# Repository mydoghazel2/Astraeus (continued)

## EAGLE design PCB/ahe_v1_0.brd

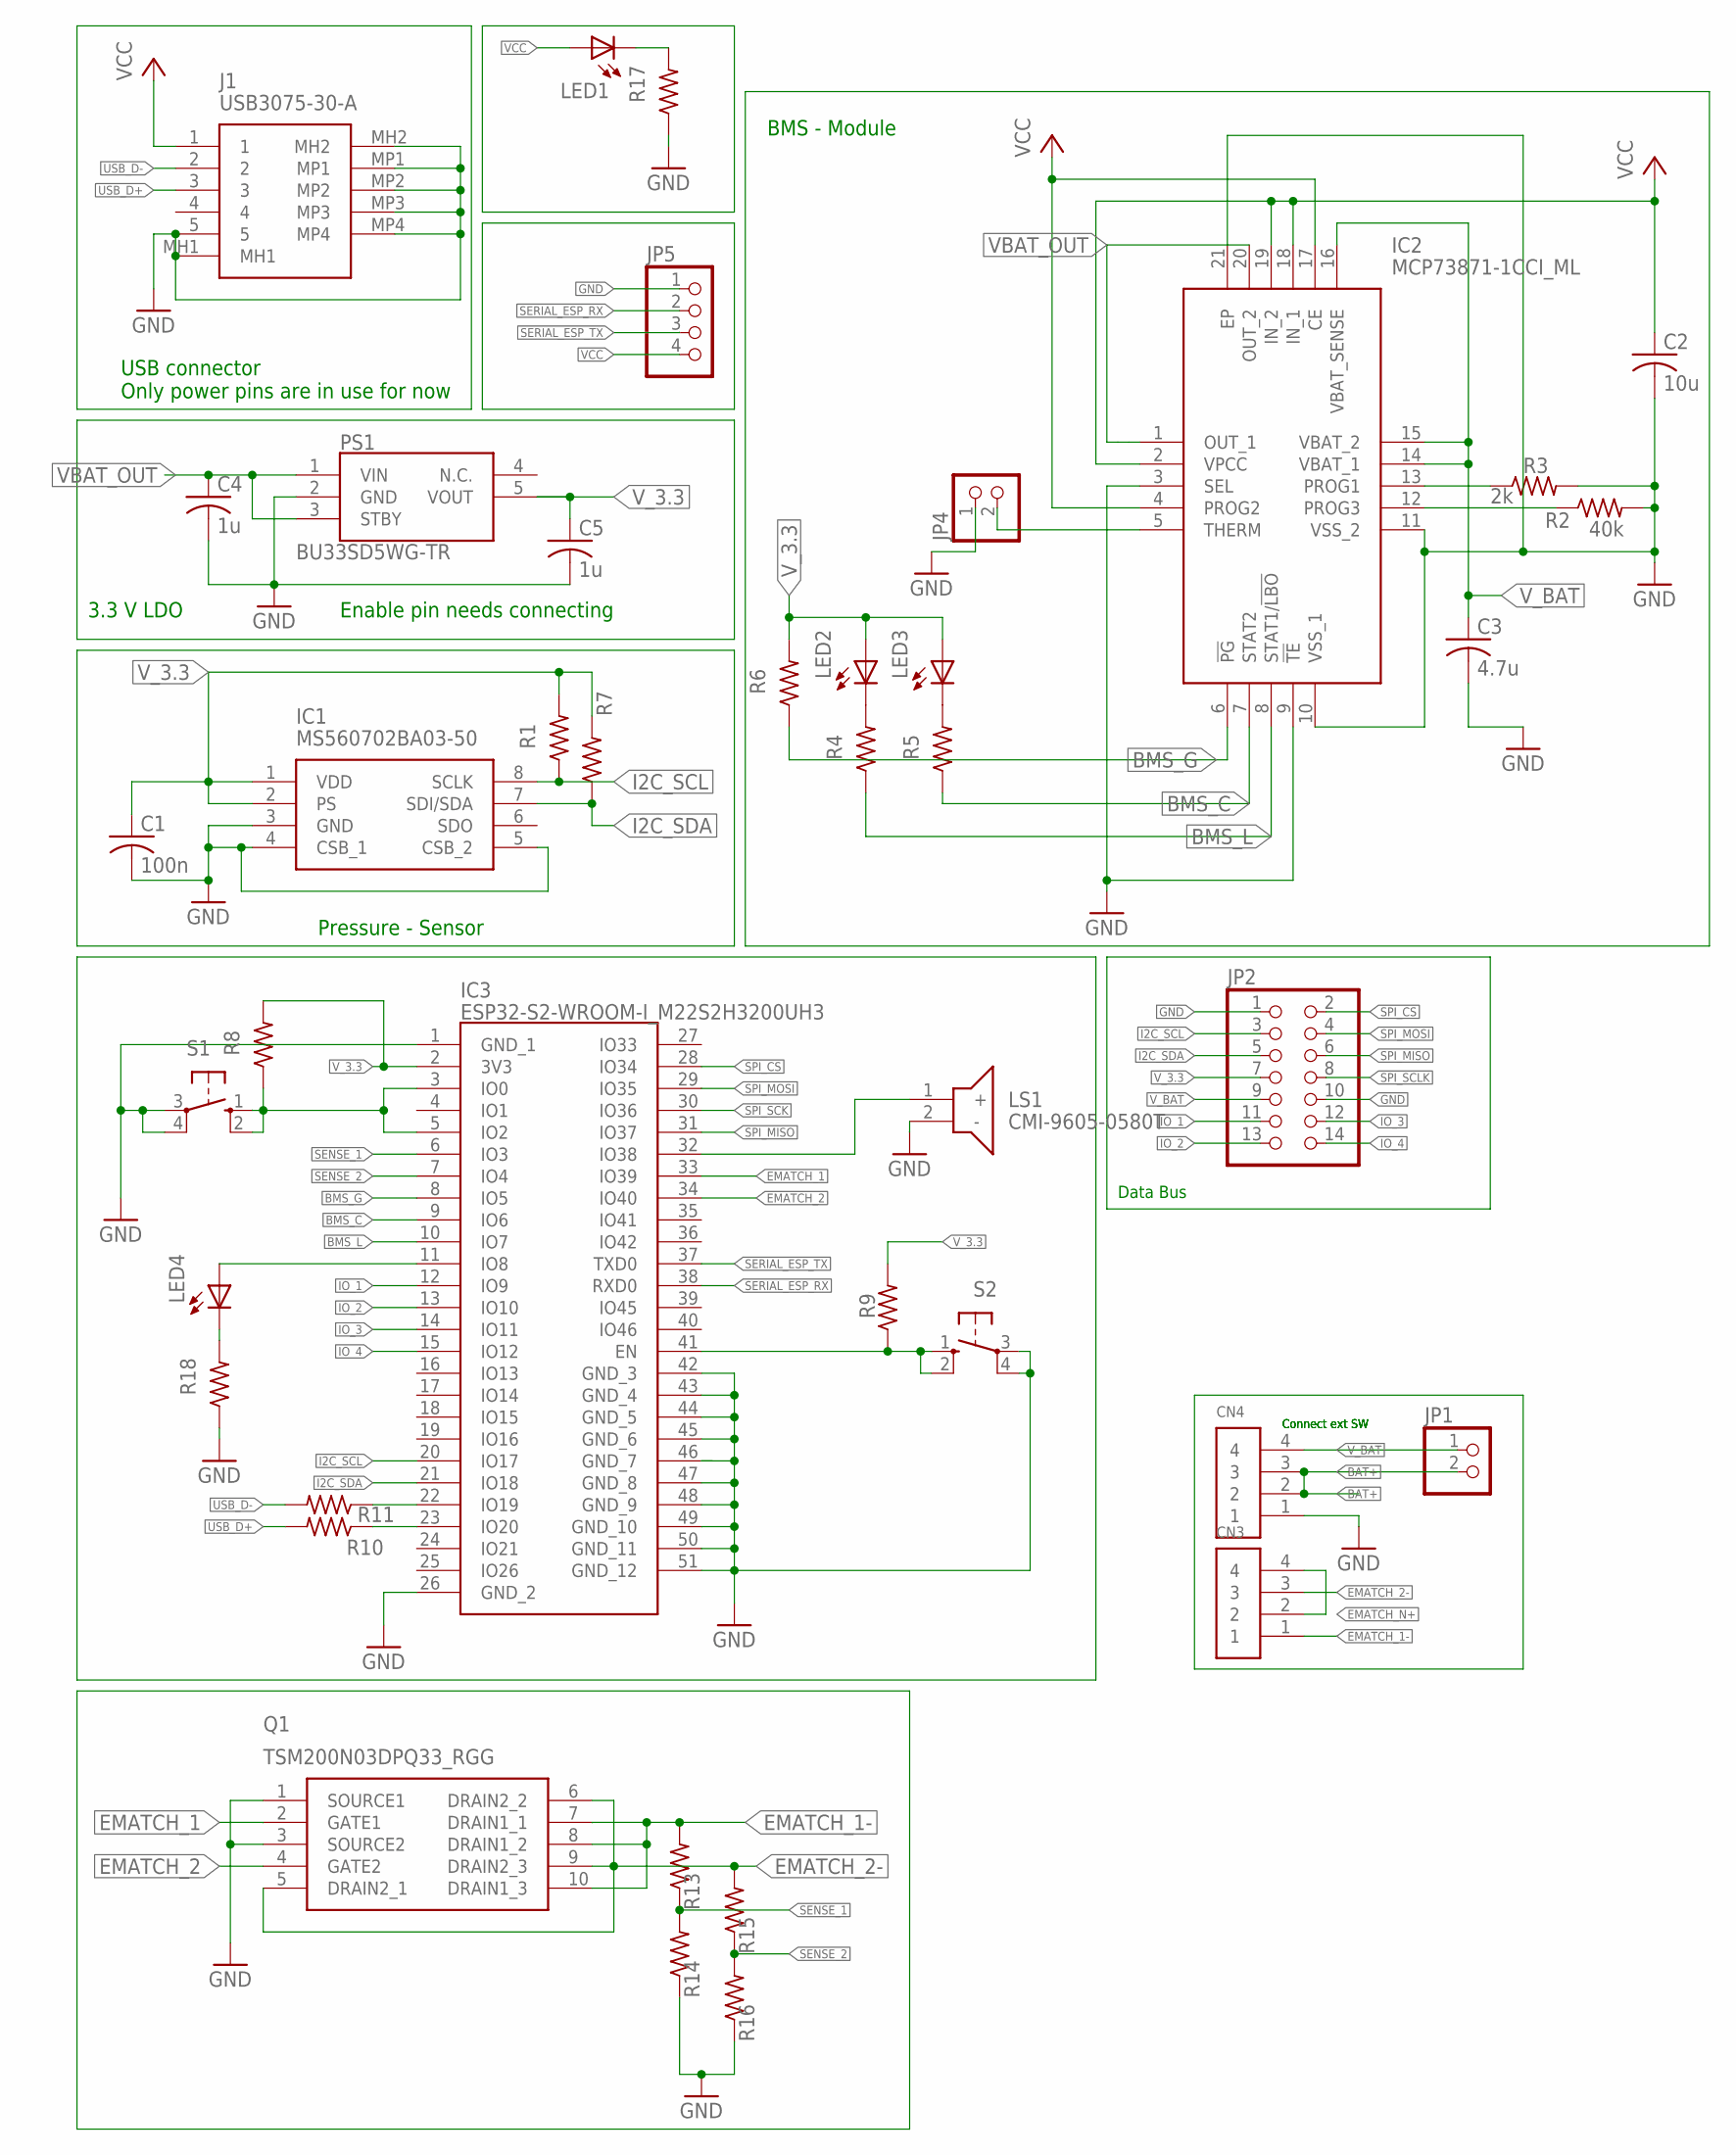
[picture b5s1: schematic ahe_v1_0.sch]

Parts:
C1: 100n; C0805
C2: 10u; C0805
C3: 4.7u; C0805
C4, C5: 1u; C0805
CN3, CN4: 1X4-3.5MM; 1X04-3.5MM
IC1: MS560702BA03-50; MS5607-02BA03
IC2: MCP73871-1CCI_ML; QFN50P400X400X100-21N
IC3: ESP32-S2-WROOM-I_M22S2H3200UH3; ESP32S2WROOMIM22S2H3200UH3Q0
J1: USB3075-30-A; USB307530A
JP1, JP4: PINHD-1X2; 1X02
JP2: PINHD-2X7; 2X07
JP5: PINHD-1X4; 1X04
LED1, LED2, LED3, LED4: LEDCHIPLED_0805; CHIPLED_0805
LS1: CMI-9605-0580T; CMI96050580T
PS1: BU33SD5WG-TR; SOT95P280X125-5N
Q1: TSM200N03DPQ33_RGG; TSM200N03DPQ33RGG
R1, R6, R7, R8, R9: 10k; R0805
R2: 40k; R0805
R3: 2k; R0805
R4, R5, R17, R18: 330; R0805
R10, R11: 33; R0805
R13, R15: 100k; R0805
R14, R16: 27k; R0805
S1, S2: 10-XX; B3F-10XX

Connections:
BAT+: CN4.2, CN4.3, JP1.2
BMS_C: IC2.7 (STAT2), IC3.9 (IO6), R5.1
BMS_G: IC2.6 (!PG), IC3.8 (IO5), R6.1
BMS_L: IC2.8 (STAT1/!LBO), IC3.10 (IO7), R4.1
EMATCH_1: IC3.33 (IO39), Q1.2 (GATE1)
EMATCH_1-: CN3.1, Q1.7 (DRAIN1_1), Q1.8 (DRAIN1_2), Q1.10 (DRAIN1_3), R13.2
EMATCH_2: IC3.34 (IO40), Q1.4 (GATE2)
EMATCH_2-: CN3.3, Q1.5 (DRAIN2_1), Q1.6 (DRAIN2_2), Q1.9 (DRAIN2_3), R15.2
EMATCH_N+: CN3.2, CN3.4
GND: C1.2, C2.2, C3.2, C4.2, C5.2, CN4.1, IC1.3 (GND), IC1.4 (CSB_1), IC1.5 (CSB_2), IC2.3 (SEL), IC2.9 (!TE), IC2.10 (VSS_1), IC2.11 (VSS_2), IC2.21 (EP), IC3.1 (GND_1), IC3.26 (GND_2), IC3.42 (GND_3), IC3.43 (GND_4), IC3.44 (GND_5), IC3.45 (GND_6), IC3.46 (GND_7), IC3.47 (GND_8), IC3.48 (GND_9), IC3.49 (GND_10), IC3.50 (GND_11), IC3.51 (GND_12), J1.5, J1.MH1, J1.MH2, J1.MP1, J1.MP2, J1.MP3, J1.MP4, JP2.1, JP2.10, JP4.1, JP5.1, LS1.2 (-), PS1.2 (GND), Q1.1 (SOURCE1), Q1.3 (SOURCE2), R2.2, R3.2, R14.1, R16.1, R17.1, R18.1, S1.3, S1.4 (P1), S2.3, S2.4 (P1)
I2C_SCL: IC1.8 (SCLK), IC3.20 (IO17), JP2.3, R1.1
I2C_SDA: IC1.7 (SDI/SDA), IC3.21 (IO18), JP2.5, R7.1
IO_1: IC3.12 (IO9), JP2.11
IO_2: IC3.13 (IO10), JP2.13
IO_3: IC3.14 (IO11), JP2.12
IO_4: IC3.15 (IO12), JP2.14
unnamed: IC2.13 (PROG1), R3.1
unnamed: IC2.12 (PROG3), R2.1
unnamed: IC2.5 (THERM), JP4.2
unnamed: IC3.3 (IO0), IC3.5 (IO2), R8.1, S1.1 (S), S1.2 (S1)
unnamed: IC3.22 (IO19), R11.1
unnamed: IC3.23 (IO20), R10.1
unnamed: LED1.C, R17.2
unnamed: LED2.C, R4.2
unnamed: LED3.C, R5.2
unnamed: LED4.C, R18.2
unnamed: IC3.11 (IO8), LED4.A
unnamed: IC3.41 (EN), R9.1, S2.1 (S), S2.2 (S1)
SENSE_1: IC3.6 (IO3), R13.1, R14.2
SENSE_2: IC3.7 (IO4), R15.1, R16.2
SERIAL_ESP_RX: IC3.38 (RXD0), JP5.2
SERIAL_ESP_TX: IC3.37 (TXD0), JP5.3
SOUND: IC3.32 (IO38), LS1.1 (+)
SPI_CS: IC3.28 (IO34), JP2.2
SPI_MISO: IC3.31 (IO37), JP2.6
SPI_MOSI: IC3.29 (IO35), JP2.4
SPI_SCK: IC3.30 (IO36)
SPI_SCLK: JP2.8
USB_D+: J1.3, R10.2
USB_D-: J1.2, R11.2
VBAT_OUT: C4.1, IC2.1 (OUT_1), IC2.20 (OUT_2), PS1.1 (VIN), PS1.3 (STBY)
VCC: C2.1, IC2.2 (VPCC), IC2.4 (PROG2), IC2.17 (CE), IC2.18 (IN_1), IC2.19 (IN_2), J1.1, JP5.4, LED1.A
V_3.3: C1.1, C5.1, IC1.1 (VDD), IC1.2 (PS), IC3.2 (3V3), JP2.7, LED2.A, LED3.A, PS1.5 (VOUT), R1.2, R6.2, R7.2, R8.2, R9.2
V_BAT: C3.1, CN4.4, IC2.14 (VBAT_1), IC2.15 (VBAT_2), IC2.16 (VBAT_SENSE), JP1.1, JP2.9

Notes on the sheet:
Pressure - Sensor
Enable pin needs connecting
USB connector Only power pins are in use for now
3.3 V LDO
BMS - Module
Data Bus
Connect ext SW

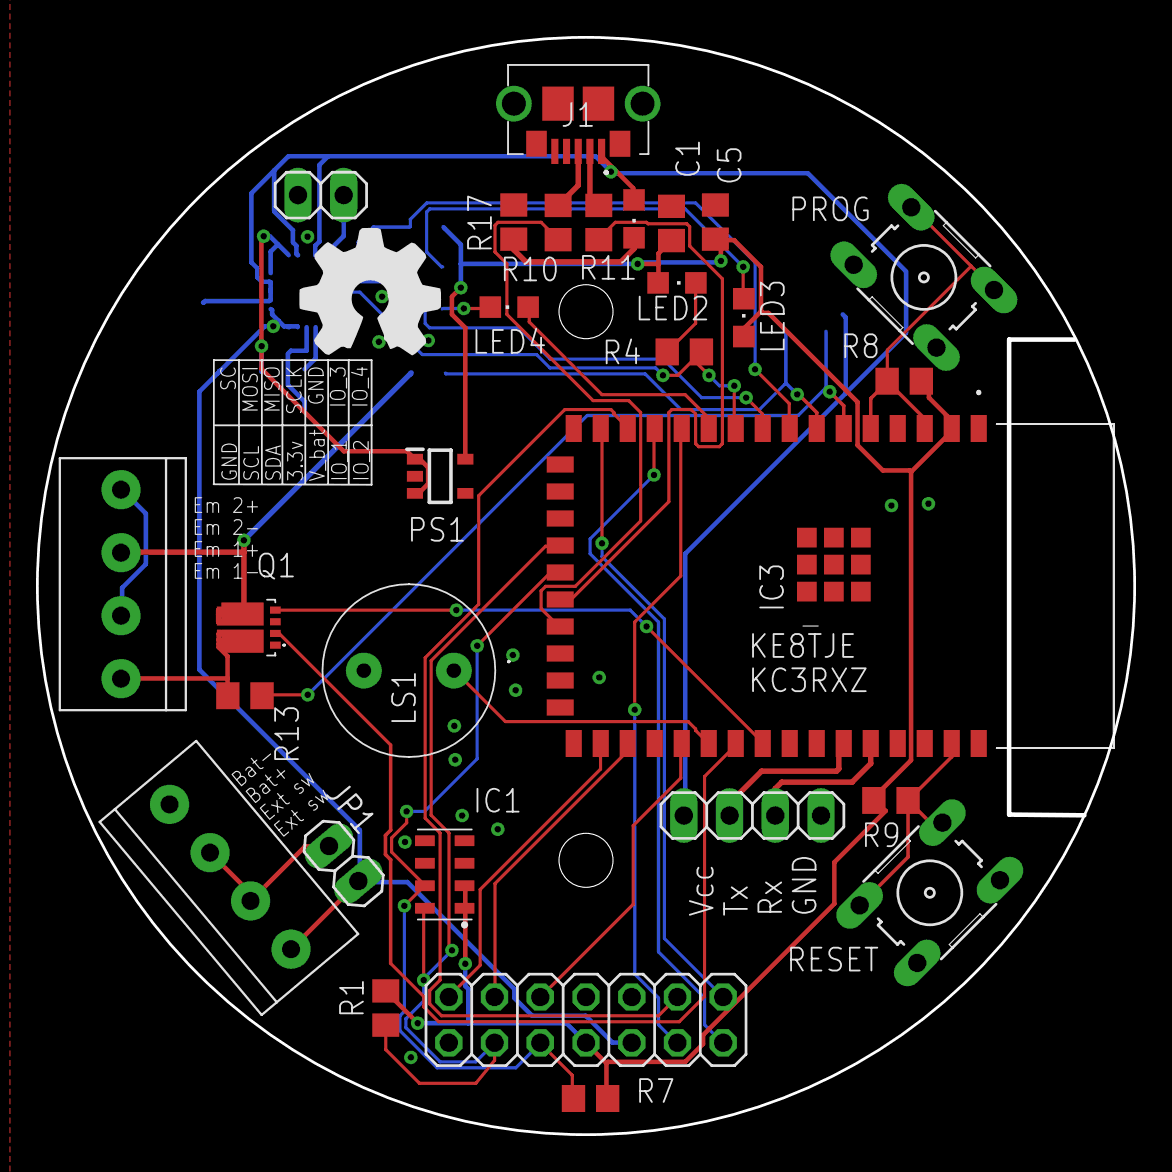
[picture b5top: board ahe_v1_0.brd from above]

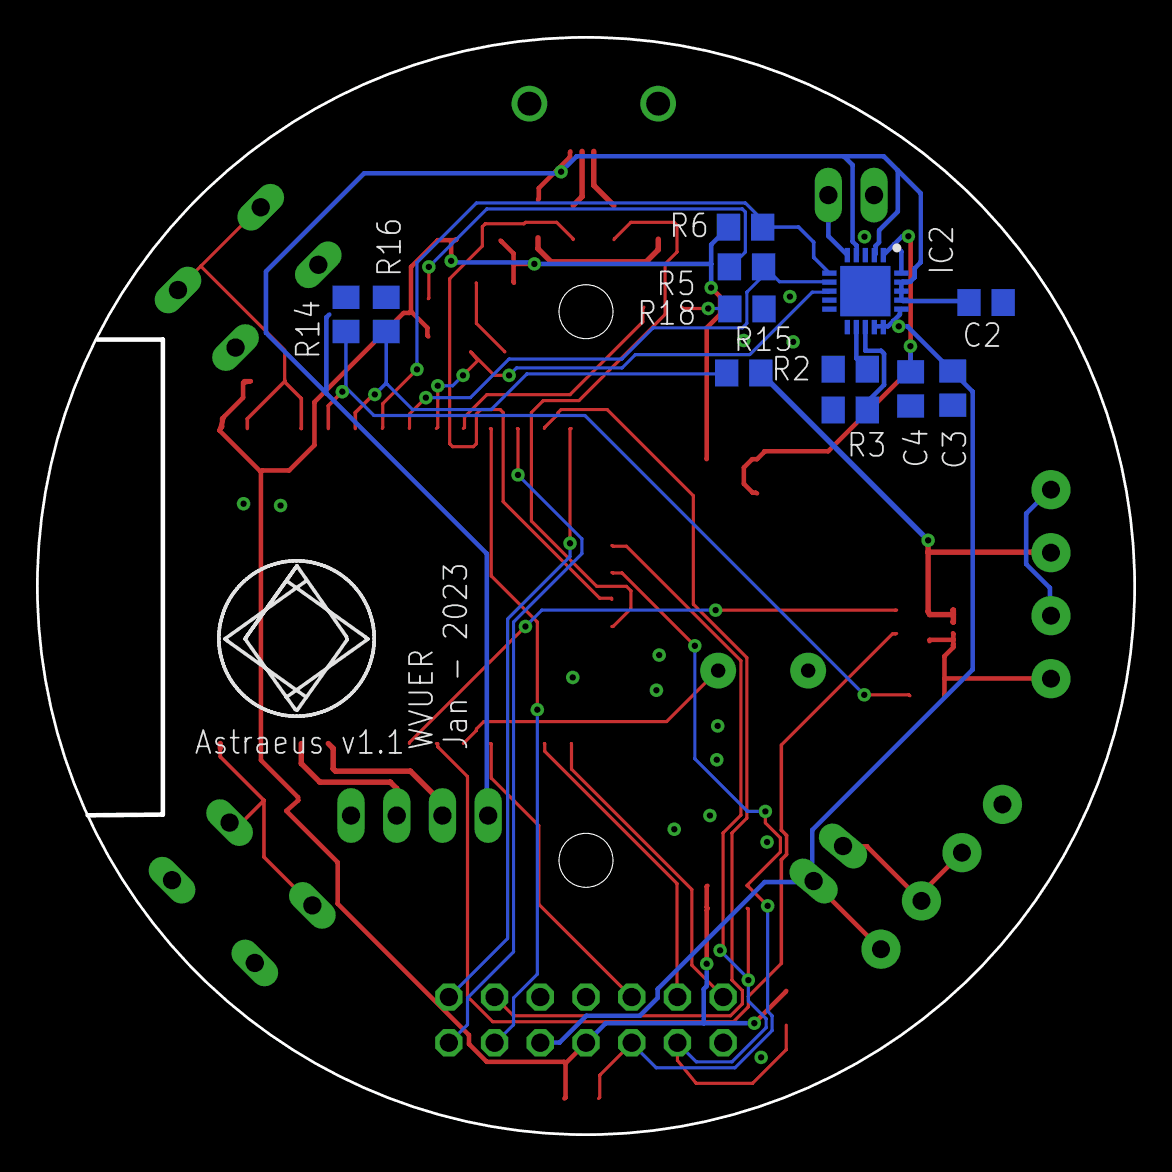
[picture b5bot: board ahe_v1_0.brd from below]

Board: 2 copper layers, 60.9 x 60.9 mm, 41 parts (12 on the bottom side), 42 nets.

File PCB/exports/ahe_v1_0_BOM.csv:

Qty,Value,Device,Package,Parts,Unit Price ,,MOUSER_PRICE-STOCK,Description,ARROW_PART_NUMBER,ARROW_PRICE-STOCK,DESCRIPTION,HEIGHT,MANUFACTURER_NAME,MANUFACTURER_PART_NUMBER,MF,MOUSER_PART_NUMBER,,MOUSER_TESTING_PART_NUMBER,MOUSER_TESTING_PRICE-STOCK,MPN,OC_FARNELL,OC_NEWARK,POPULARITY,SPICEPREFIX
2,,10-XX,B3F-10XX,"S1, S2",,0,,OMRON SWITCH,,,,,,,,,,,,B3F-1000,176432,36M3542,72,
1,,PINHD-1X4/90,1X04/90,JP3,,0,,PIN HEADER,,,,,,,,,,,,,,,9,
1,,PINHD-2X7,2X07,JP2,,0,,PIN HEADER,,,,,,,,,,,,,,,8,
1,0,R-US_R0805,R0805,R12,0,0,,"RESISTOR, American symbol",,,,,,,,,,,,,,,85,R
2,100k,R-US_R0805,R0805,"R13, R15",0.15,0.3,https://www.mouser.com/ProductDetail/Vishay-Draloric/RCG0805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,"RESISTOR, American symbol",,,,,,,,,,,,,,,85,R
1,100n,C-USC0805,C0805,C1,0.15,0.15,,"CAPACITOR, American symbol",,,,,,,,,,,,,,,63,C
1,103KT1005T-1P,103KT1005T-1P,THRMC1005X60N,RT1,0.3,0.3,https://www.mouser.co.uk/ProductDetail/Semitec/103KT1005T-1P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,NTC Thermistors 103kohm 1% 0402,,,NTC Thermistors 103kohm 1% 0402,0.6mm,Semitec,103KT1005T-1P,,954-103KT1005T-1P,,,,,,,,
7,10k,R-US_R0805,R0805,"R1, R4, R5, R6, R7, R8, R9",0.15,1.05,https://www.mouser.com/ProductDetail/Vishay-Draloric/RCG0805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,"RESISTOR, American symbol",,,,,,,,,,,,,,,85,R
1,10u,C-USC0805,C0805,C2,0.15,0.15,,"CAPACITOR, American symbol",,,,,,,,,,,,,,,63,C
2,1X4-3.5MM,1X4-3.5MM,1X04-3.5MM,"CN1, CN2",0.59,1.18,https://www.adafruit.com/product/724,4-pin connector,,,,,,,,,,,,,,,,
2,1u,C-USC0805,C0805,"C4, C5",0.15,0.3,,"CAPACITOR, American symbol",,,,,,,,,,,,,,,63,C
2,27k,R-US_R0805,R0805,"R14, R16",0.15,0.3,,"RESISTOR, American symbol",,,,,,,,,,,,,,,85,R
1,2k,R-US_R0805,R0805,R3,0.15,0.15,,"RESISTOR, American symbol",,,,,,,,,,,,,,,85,R
2,33,R-US_R0805,R0805,"R10, R11",0.15,0.3,,"RESISTOR, American symbol",,,,,,,,,,,,,,,85,R
1,4.7u,C-USC0805,C0805,C3,0.15,0.15,,"CAPACITOR, American symbol",,,,,,,,,,,,,,,63,C
1,40k,R-US_R0805,R0805,R2,0.15,0.15,,"RESISTOR, American symbol",,,,,,,,,,,,,,,85,R
1,BU33SD5WG-TR,BU33SD5WG-TR,SOT95P280X125-5N,PS1,0.61,0.61,https://www.mouser.co.uk/ProductDetail/ROHM-Semiconductor/BU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,"LDO regulator,3.3V,0.5A,standby,SSOP5 ROHM BU33SD5WG-TR, LDO Voltage Regulator, 0.5A, 3.3 V +/-2%, 1.7  6 Vin, 5-Pin SSOP",,,"LDO regulator,3.3V,0.5A,standby,SSOP5 ROHM BU33SD5WG-TR, LDO Voltage Regulator, 0.5A, 3.3 V +/-2%, 1.7  6 Vin, 5-Pin SSOP",1.25mm,ROHM Semiconductor,BU33SD5WG-TR,,755-BU33SD5WG-TR,,,,,,,,
1,CMI-9605-0580T,CMI-9605-0580T,CMI96050580T,LS1,1.33,1.33,https://www.mouser.co.uk/ProductDetail/CUI-Devices/CMI-9605-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,"Piezo Buzzers & Audio Indicators buzzer, 9.6 mm x 5 mm deep, M, 5 VDC, 80 dB, Through Hole, Audio Indicator",,,"Piezo Buzzers & Audio Indicators buzzer, 9.6 mm x 5 mm deep, M, 5 VDC, 80 dB, Through Hole, Audio Indicator",5mm,CUI Inc.,CMI-9605-0580T,,490-CMI-9605-0580T,,,,,,,,
1,ESP32-S2-WROOM-I_M22S2H3200UH3,ESP32-S2-WROOM-I_M22S2H3200UH3,ESP32S2WROOMIM22S2H3200UH3Q0,IC3,2.13,2.13,https://www.mouser.co.uk/ProductDetail/Espressif-Systems/ESP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,WiFi Modules (802.11) Module ESP32-S2 WROOM IPEX ANT,,,WiFi Modules (802.11) Module ESP32-S2 WROOM IPEX ANT,3.45mm,Espressif Systems,ESP32-S2-WROOM-I(M22S2H3200UH3Q0),,356-ESP32S2WRMI320UH,,,,,,,,
1,MCP73871-1CCI_ML,MCP73871-1CCI_ML,QFN50P400X400X100-21N,IC2,2.42,2.42,https://www.mouser.co.uk/ProductDetail/Microchip-Technology-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,Battery Management USB/AC Battery Charger w/Pwr Mgmt,,,Battery Management USB/AC Battery Charger w/Pwr Mgmt,1mm,Microchip,MCP73871-1CCI/ML,,579-MCP73871-1CCI/ML,,,,,,,,
1,MS560702BA03-50,MS560702BA03-50,MS5607-02BA03,IC1,5.44,5.44,https://www.mouser.co.uk/ProductDetail/Measurement-Specialti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,"MS560702BA03-50, Barometric Pressure Sensor, 1200mbar 0  3.6 V Output, 8-Pin QFN",,,"MS560702BA03-50, Barometric Pressure Sensor, 1200mbar 0  3.6 V Output, 8-Pin QFN",mm,TE Connectivity,MS560702BA03-50,,824-MS560702BA03-50,,,,,,,,
1,TSM200N03DPQ33_RGG,TSM200N03DPQ33_RGG,TSM200N03DPQ33RGG,Q1,1.76,1.76,https://www.mouser.co.uk/ProductDetail/Taiwan-Semiconductor/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,"MOSFET MOSFET, Dual, N-Ch Trench, 30V, 20A",,,"MOSFET MOSFET, Dual, N-Ch Trench, 30V, 20A",0.8mm,Taiwan Semiconductor,TSM200N03DPQ33 RGG,,821-TSM200N03DPQ33RG,,,,,,,,
1,USB3075-30-A,USB3075-30-A,USB307530A,J1,0.7,0.7,https://www.mouser.co.uk/ProductDetail/GCT/USB3075-30-A?qs=K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,"GCT (GLOBAL CONNECTOR TECHNOLOGY) - USB3075-30-A - USB Connector, Micro USB Type B, USB 2.0, Receptacle, 5 Ways, Surface Mount, Right Angle",,,"GCT (GLOBAL CONNECTOR TECHNOLOGY) - USB3075-30-A - USB Connector, Micro USB Type B, USB 2.0, Receptacle, 5 Ways, Surface Mount, Right Angle",2.7mm,GCT (GLOBAL CONNECTOR TECHNOLOGY),USB3075-30-A,,640-USB3075-30-A,,,,,,,,
,,,,,,18.87,,,,,,,,,,,,,,,,,,

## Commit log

2023-02-24 Add board layout printable PDF
2023-03-04 Fixed known BMS issues
2023-03-24 backup board added for N8MDC
2023-03-25 APRS module initial design
2023-03-25 single side routing
2023-03-28 added a v2 board which uses a nano
2023-03-28 added 5v connector
2023-03-28 fix VCC and Vin
2023-03-28 updated the readme with aprs v2.0
2023-03-28 added the image
2023-03-29 added top and fixed the jumper for final build
2023-03-31 Initial work from testing
2023-03-31 radio mods
2023-04-01 Add files via upload
    This is the working code for the PCB version 2.0
2023-04-03 Add files via upload
    Schematic for the teensy main board, incomplete
2023-04-04 Add files via upload
    Updated and working Teensy Main board, needs breadboarded and tested fully
2023-04-04 Delete Teensy_Main.sch
    Re-design file that would've ended up being more work since I had already made most of the board previously
2023-04-05 Add files via upload
    Update with routing and no usb connector anymore
2023-04-05 rerouted the main board. one pin pending
2023-04-05 fix file issues
2023-04-05 Add files via upload
    Version 1.2, One sided board for test flight
2023-04-05 Add files via upload
    V1.2, Test ready, Added decals
2023-04-05 Add files via upload
    Fixed silly little airwire due to decals
2023-04-27 Updated to un-include references
